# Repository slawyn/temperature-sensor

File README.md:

This project focuses on creating a simple usb-powered hardware that measures temperature.
*v1 - initial faulty design. CA CK have for 7-segment been switched
*v2 - improved doubled-sided design. Potentiometer replaced by an digital spi controller poti. Problem with the vias.
*v3 - wip

Use "Gerberlogix" to viewer gerber files.

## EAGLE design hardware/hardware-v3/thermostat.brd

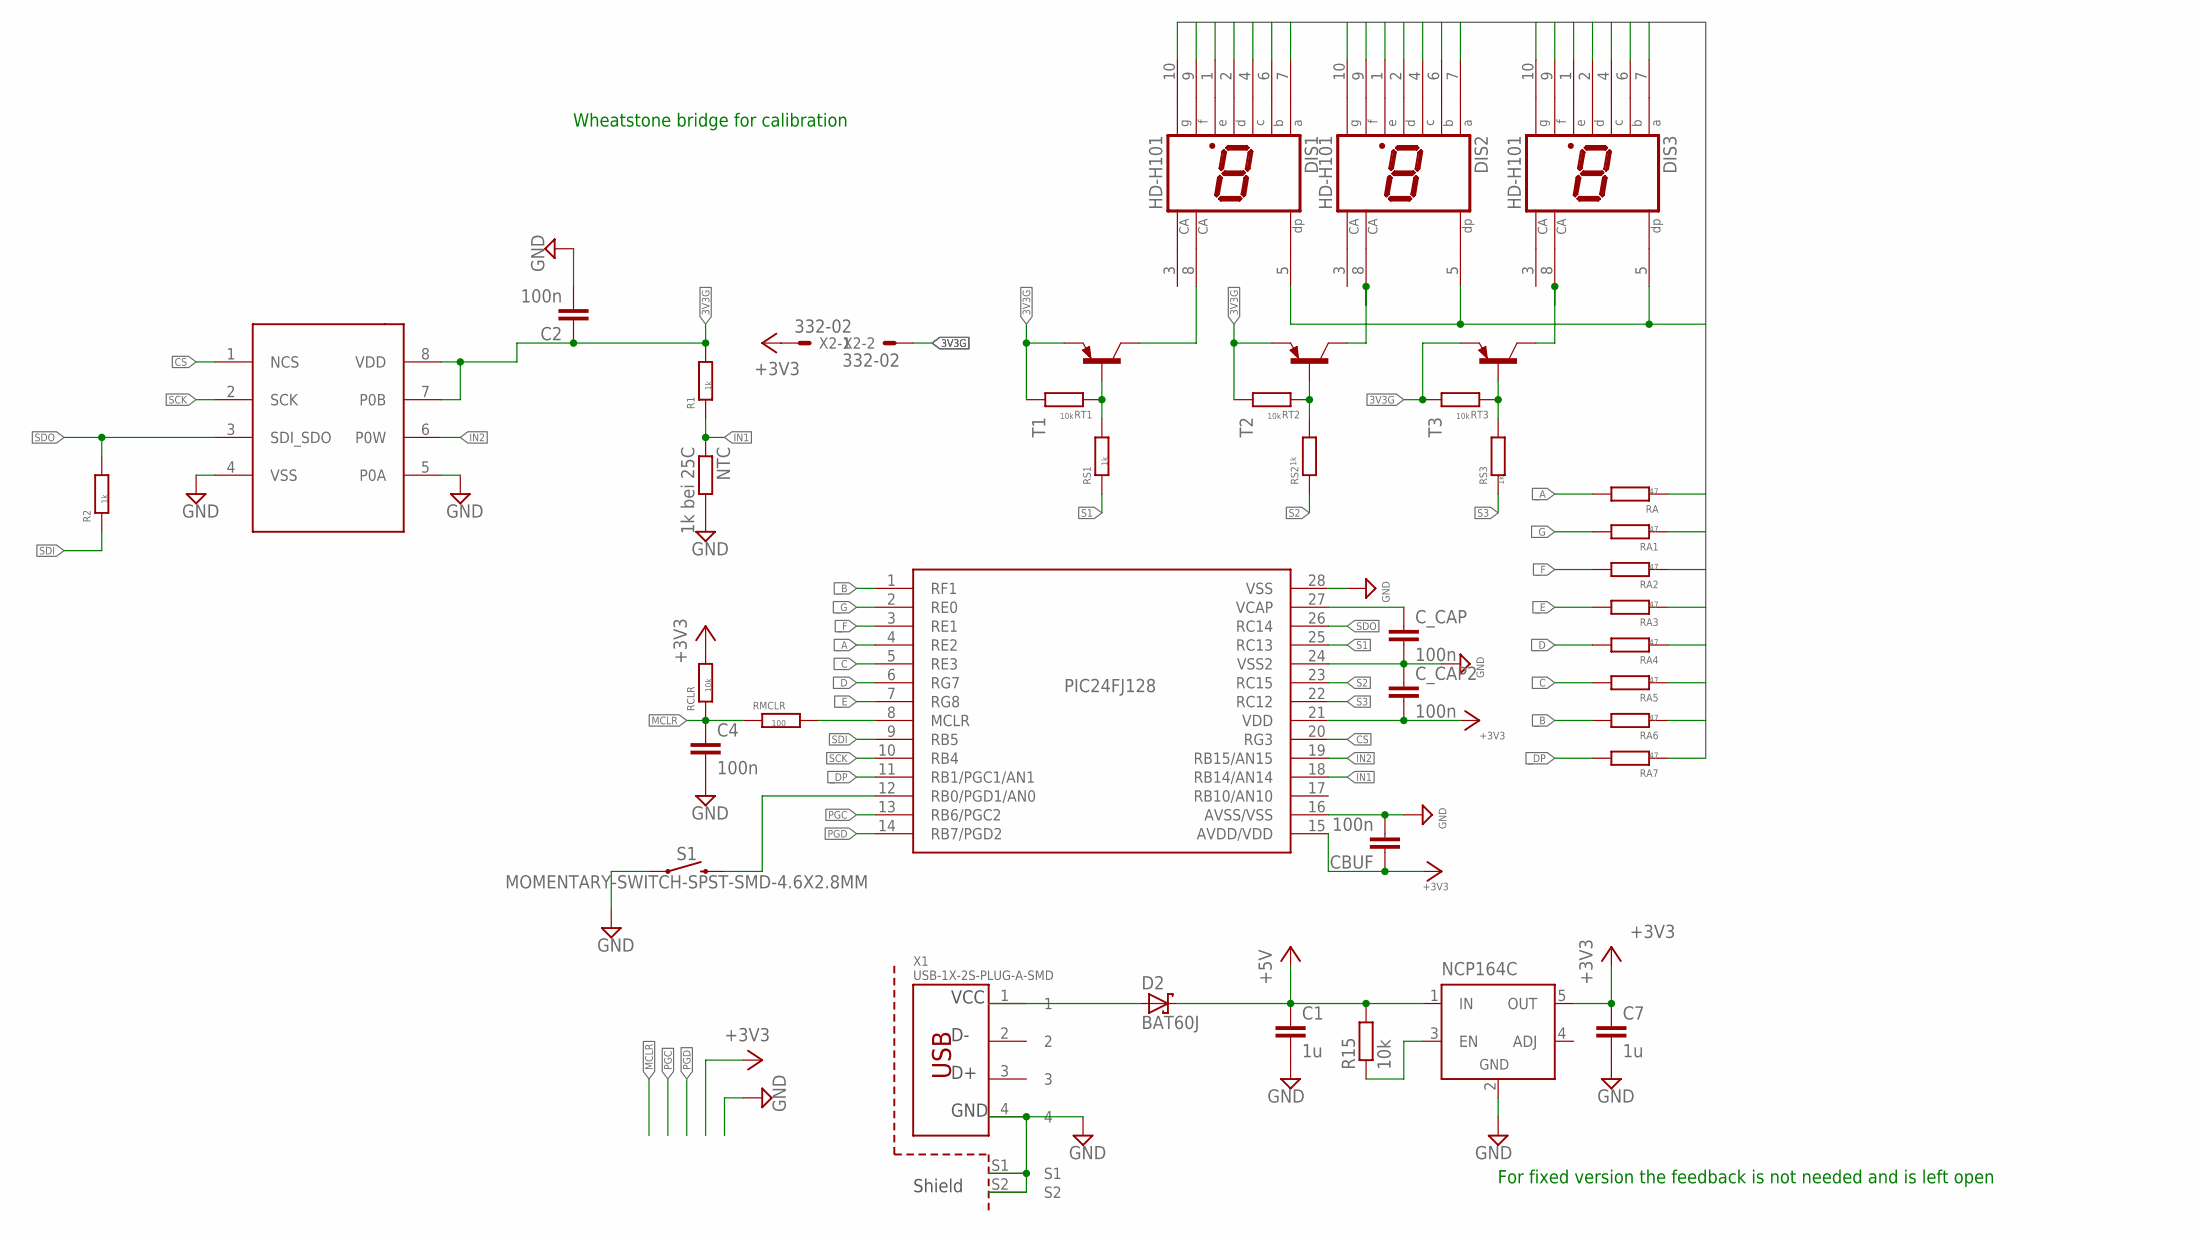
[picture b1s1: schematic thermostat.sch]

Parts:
C1, C7: 1u; C0603
C2, C4: 100n; C0603
CBUF: 100n; C0603
C_CAP, C_CAP2: 100n; C0603
D2: BAT60J; SOD323_ST
DIS1, DIS2, DIS3: HD-H101; HDSP-M
NCP164C: -; TSOP-5
NTC: 1k bei 25C; 0204V
R1, R2: 1k; R0603
R15: 10k; R0603
RA, RA1, RA2, RA3, RA4, RA5, RA6, RA7: 47; R0603
RCLR: 10k; R0603
RMCLR: 100; R0603
RS1, RS2, RS3: 1k; R0603
RT1, RT2, RT3: 10k; R0603
S1: MOMENTARY-SWITCH-SPST-SMD-4.6X2.8MM; TACTILE_SWITCH_SMD_4.6X2.8MM
T1, T2, T3: -PNP-SOT23-BCE; SOT23-BCE
U$1: MCP4151; SO-08
U$2: -; SSOP28
X1: USB-1X-2S-PLUG-A-SMD; USB-PLUG-A-SMD-2S
X2: 332-02

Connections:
3V3G: C2.1, R1.2, RT1.2, RT2.2, RT3.2, T1.E, T2.E, T3.E, U$1.7 (P0B), U$1.8 (VDD), X2.2
+3V3: C7.1, CBUF.1, C_CAP2.2, NCP164C.5 (OUT), RCLR.2, U$2.15 (AVDD/VDD), U$2.21 (VDD), X2.1
+5V: C1.1, D2.C, NCP164C.1 (IN), R15.2
A: DIS1.7 (A), DIS2.7 (A), DIS3.7 (A), RA.1
B: DIS1.6 (B), DIS2.6 (B), DIS3.6 (B), RA6.1
C: DIS1.4 (C), DIS2.4 (C), DIS3.4 (C), RA5.1
CS: U$1.1 (NCS), U$2.20 (RG3)
D: DIS1.2 (D), DIS2.2 (D), DIS3.2 (D), RA4.1
DP: DIS1.5 (DP), DIS2.5 (DP), DIS3.5 (DP), RA7.1
E: DIS1.1 (E), DIS2.1 (E), DIS3.1 (E), RA3.1
F: DIS1.9 (F), DIS2.9 (F), DIS3.9 (F), RA2.1
G: DIS1.10 (G), DIS2.10 (G), DIS3.10 (G), RA1.1
GND: C1.2, C2.2, C4.2, C7.2, CBUF.2, C_CAP.2, C_CAP2.1, NCP164C.2 (GND), NTC.2, S1.1, S1.2 (1), U$1.4 (VSS), U$1.5 (P0A), U$2.16 (AVSS/VSS), U$2.24 (VSS2), U$2.28 (VSS), X1.4, X1.S1, X1.S2
IN1: NTC.1, R1.1, U$2.18 (RB14/AN14)
IN2: U$1.6 (P0W), U$2.19 (RB15/AN15)
MCLR: C4.1, RCLR.1, RMCLR.1
unnamed: NCP164C.3 (EN), R15.1
unnamed: C_CAP.1, U$2.27 (VCAP)
unnamed: RS1.2, RT1.1, T1.B
unnamed: D2.A, X1.1
unnamed: RMCLR.2, U$2.8 (MCLR)
unnamed: RS3.2, RT3.1, T3.B
unnamed: RS2.2, RT2.1, T2.B
unnamed: DIS1.8 (CA), T1.C
unnamed: DIS2.8 (CA), T2.C
unnamed: DIS3.8 (CA), T3.C
unnamed: S1.3 (2), S1.4 (2), U$2.12 (RB0/PGD1/AN0)
PGC: U$2.13 (RB6/PGC2)
PGD: U$2.14 (RB7/PGD2)
S1: RS1.1, U$2.25 (RC13)
S2: RS2.1, U$2.23 (RC15)
S3: RS3.1, U$2.22 (RC12)
SCK: U$1.2 (SCK), U$2.10 (RB4)
SDI: R2.1, U$2.9 (RB5)
SDO: R2.2, U$1.3 (SDI_SDO), U$2.26 (RC14)
_A: RA.2, U$2.4 (RE2)
_B: RA6.2, U$2.1 (RF1)
_C: RA5.2, U$2.5 (RE3)
_D: RA4.2, U$2.6 (RG7)
_DP: RA7.2, U$2.11 (RB1/PGC1/AN1)
_E: RA3.2, U$2.7 (RG8)
_F: RA2.2, U$2.3 (RE1)
_G: RA1.2, U$2.2 (RE0)

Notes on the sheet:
For fixed version the feedback is not needed and is left open
Wheatstone bridge for calibration

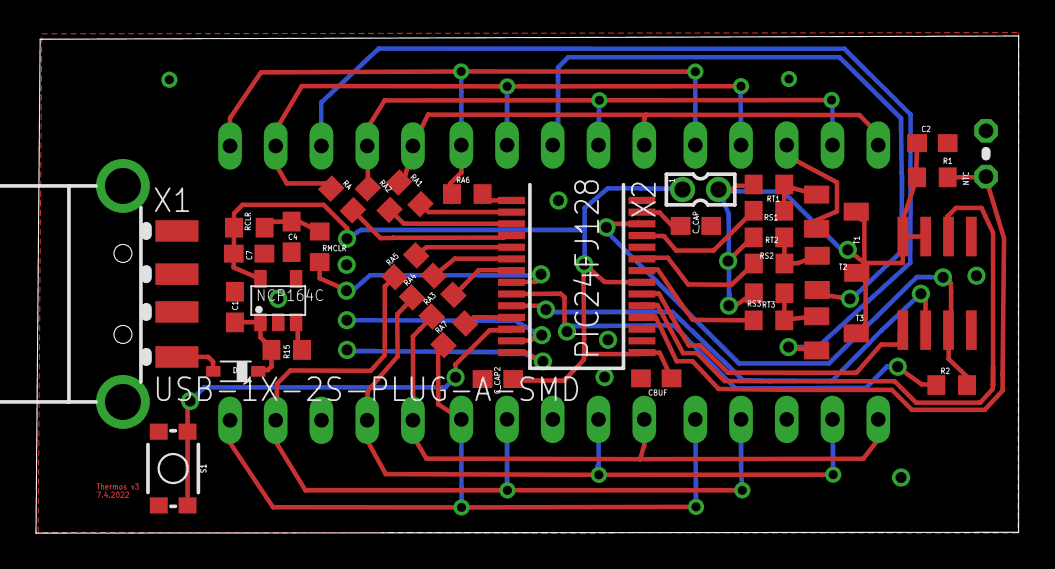
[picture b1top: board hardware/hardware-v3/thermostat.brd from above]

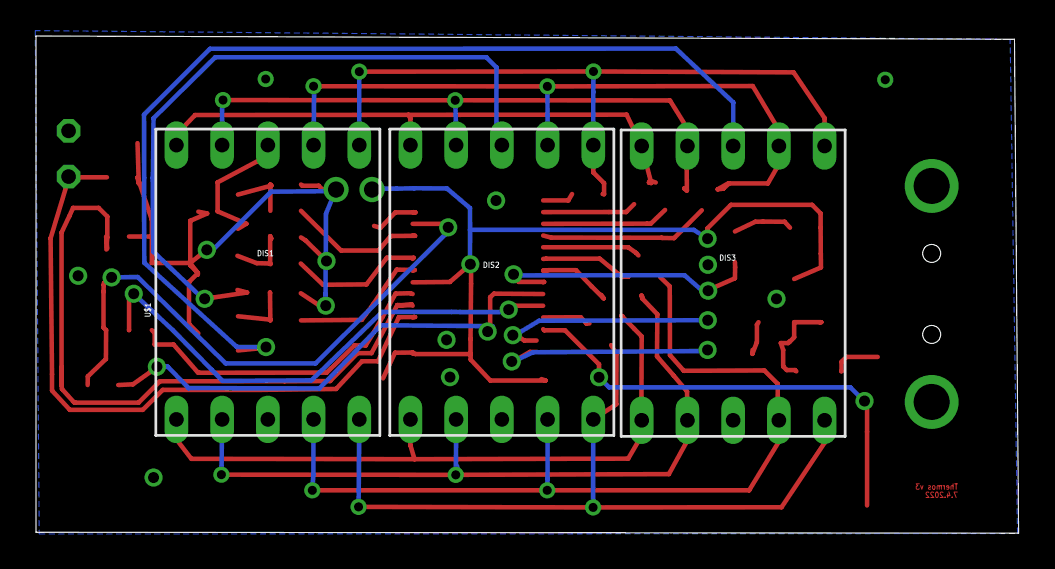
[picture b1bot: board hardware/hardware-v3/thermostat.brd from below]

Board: 2 copper layers, 54.6 x 27.6 mm, 40 parts (3 on the bottom side), 41 nets.

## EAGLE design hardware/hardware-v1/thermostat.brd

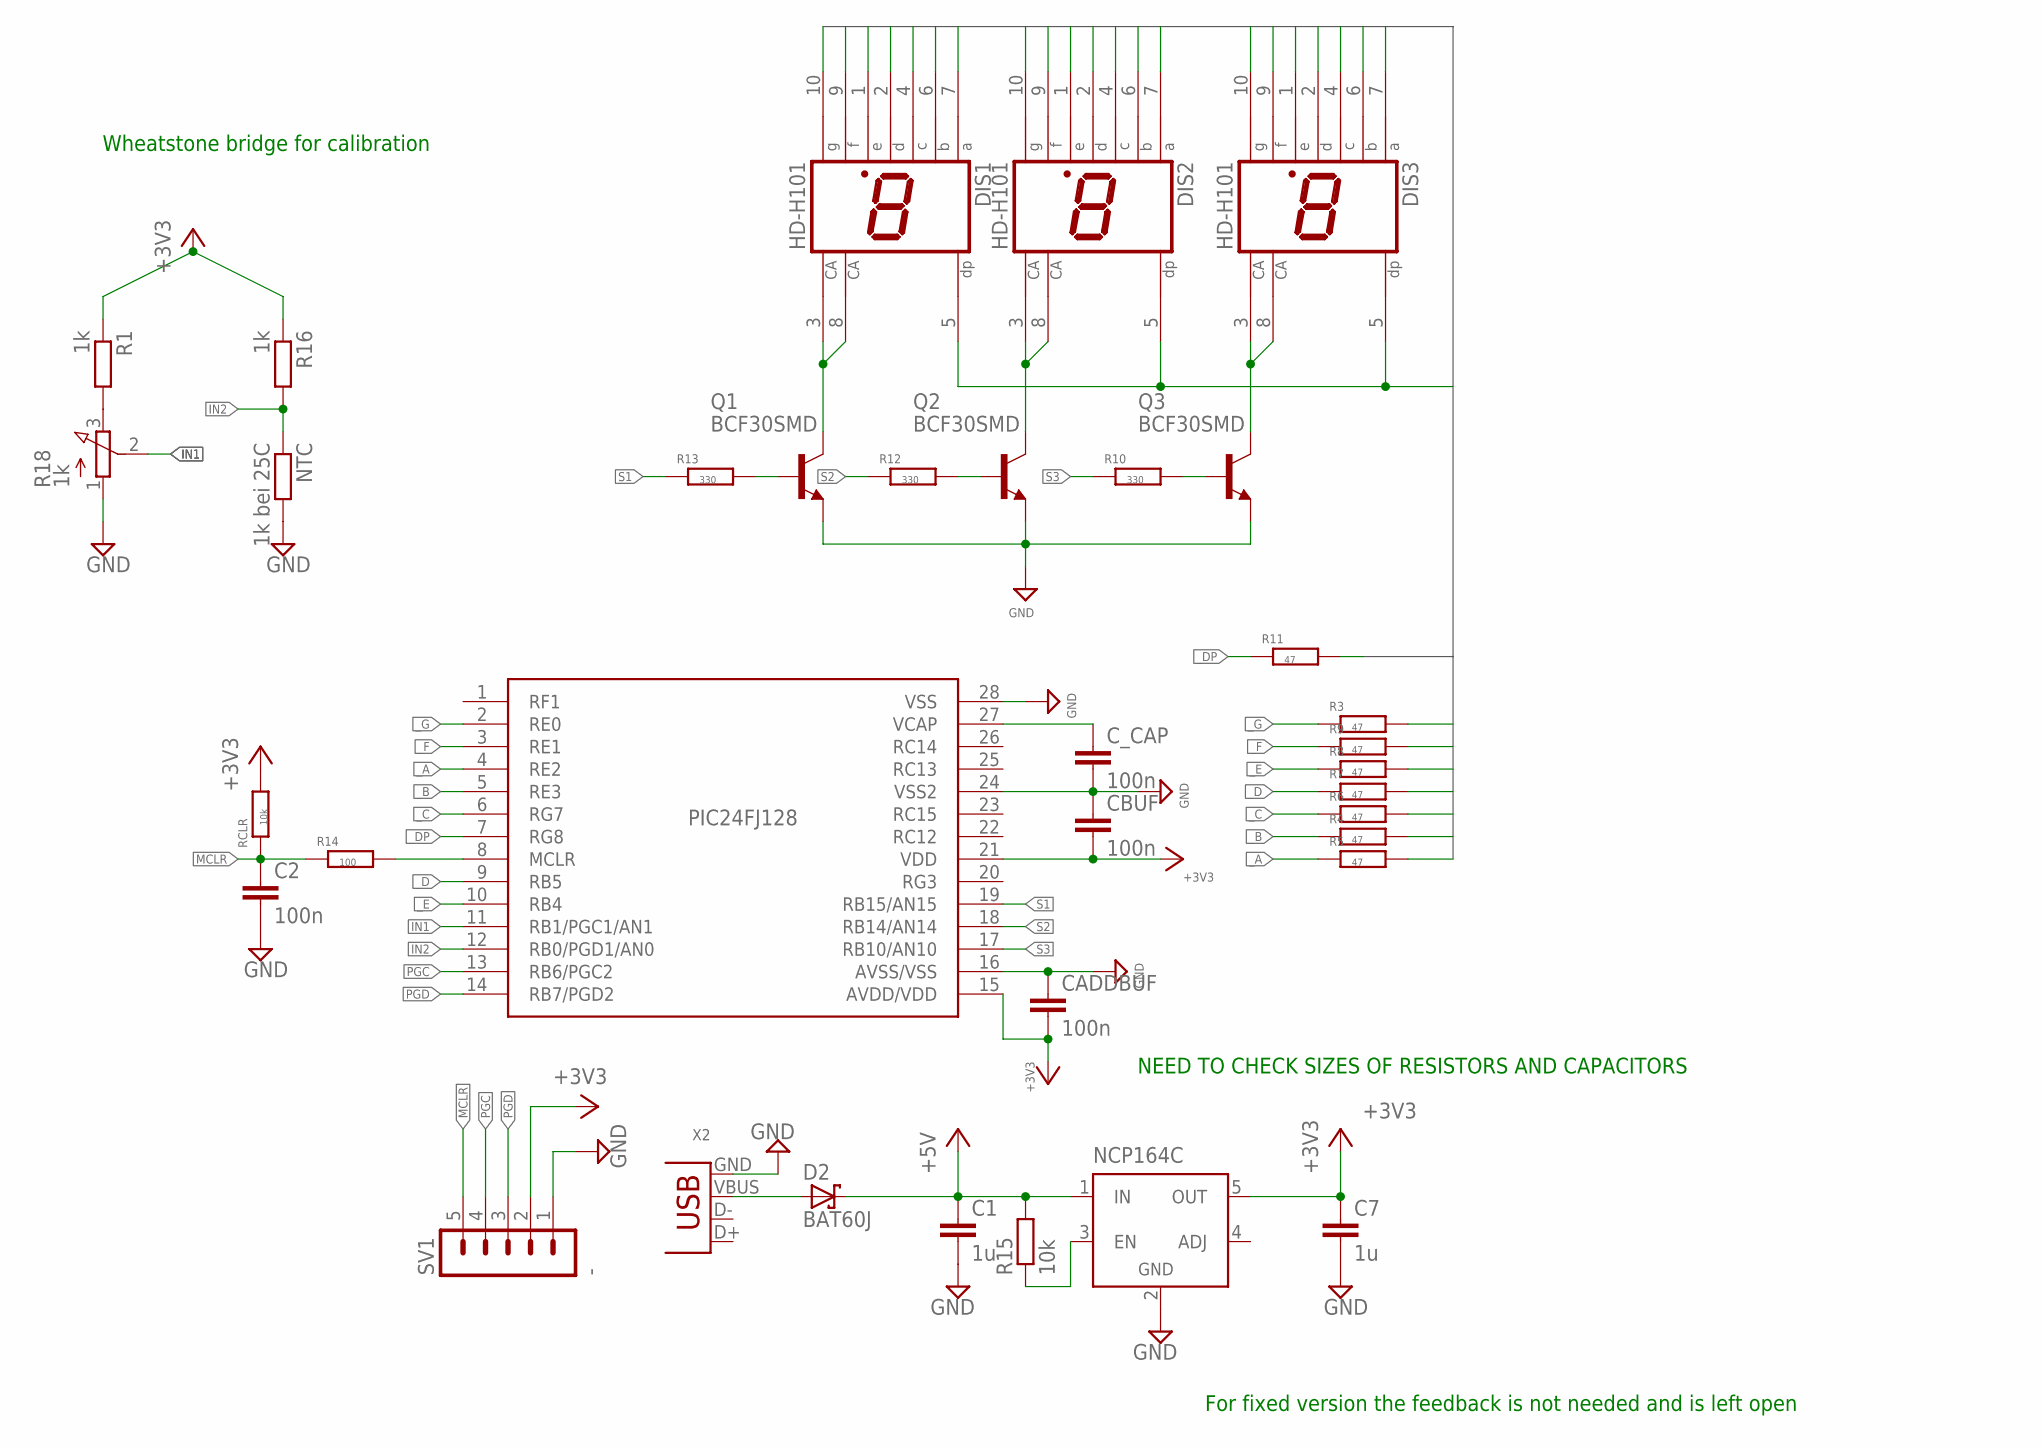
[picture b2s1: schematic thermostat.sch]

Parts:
C1, C7: 1u; C0603
C2: 100n; C0805
CADDBUF: 100n; C0603
CBUF: 100n; C0603
C_CAP: 100n; C0603
D2: BAT60J; SOD323_ST
DIS1, DIS2, DIS3: HD-H101; HDSP-M
NCP164C: -; TSOP-5
NTC: 1k bei 25C; 0204V
Q1, Q2, Q3: BCF30SMD; SOT23-BEC
R1, R16: 1k; R2010
R3, R4, R5, R6, R7, R8, R9, R11: 47; R0603
R10, R12, R13: 330; R0603
R14: 100; R0603
R15: 10k; R0603
R18: 1k; 3RP/1610N
RCLR: 10k; R0603
SV1: -; MA05-1
U$2: -; SSOP28
X2: -; USB-A-S

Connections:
+3V3: C7.1, CADDBUF.2, CBUF.2, NCP164C.5 (OUT), R1.1, R16.1, RCLR.2, SV1.2, U$2.15 (AVDD/VDD), U$2.21 (VDD)
+5V: C1.1, D2.C, NCP164C.1 (IN), R15.2
A: DIS1.7 (A), DIS2.7 (A), DIS3.7 (A), R5.2
B: DIS1.6 (B), DIS2.6 (B), DIS3.6 (B), R4.2
C: DIS1.4 (C), DIS2.4 (C), DIS3.4 (C), R6.2
D: DIS1.2 (D), DIS2.2 (D), DIS3.2 (D), R7.2
DP: DIS1.5 (DP), DIS2.5 (DP), DIS3.5 (DP), R11.2
E: DIS1.1 (E), DIS2.1 (E), DIS3.1 (E), R8.2
F: DIS1.9 (F), DIS2.9 (F), DIS3.9 (F), R9.2
G: DIS1.10 (G), DIS2.10 (G), DIS3.10 (G), R3.2
GND: C1.2, C2.2, C7.2, CADDBUF.1, CBUF.1, C_CAP.2, NCP164C.2 (GND), NTC.2, Q1.E, Q2.E, Q3.E, R18.1 (A), SV1.1, U$2.16 (AVSS/VSS), U$2.24 (VSS2), U$2.28 (VSS), X2.GND
IN1: R18.2 (S), U$2.11 (RB1/PGC1/AN1)
IN2: NTC.1, R16.2, U$2.12 (RB0/PGD1/AN0)
MCLR: C2.1, R14.1, RCLR.1, SV1.5
unnamed: NCP164C.3 (EN), R15.1
unnamed: R1.2, R18.3 (E)
unnamed: C_CAP.1, U$2.27 (VCAP)
unnamed: D2.A, X2.VBUS
unnamed: R14.2, U$2.8 (MCLR)
unnamed: DIS1.3 (CA), DIS1.8 (CA), Q1.C
unnamed: DIS2.3 (CA), DIS2.8 (CA), Q2.C
unnamed: DIS3.3 (CA), DIS3.8 (CA), Q3.C
unnamed: Q1.B, R13.2
unnamed: Q2.B, R12.2
unnamed: Q3.B, R10.2
PGC: SV1.4, U$2.13 (RB6/PGC2)
PGD: SV1.3, U$2.14 (RB7/PGD2)
S1: R13.1, U$2.19 (RB15/AN15)
S2: R12.1, U$2.18 (RB14/AN14)
S3: R10.1, U$2.17 (RB10/AN10)
_A: R5.1, U$2.4 (RE2)
_B: R4.1, U$2.5 (RE3)
_C: R6.1, U$2.6 (RG7)
_D: R7.1, U$2.9 (RB5)
_DP: R11.1, U$2.7 (RG8)
_E: R8.1, U$2.10 (RB4)
_F: R9.1, U$2.3 (RE1)
_G: R3.1, U$2.2 (RE0)

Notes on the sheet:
NEED TO CHECK SIZES OF RESISTORS AND CAPACITORS
For fixed version the feedback is not needed and is left open
Wheatstone bridge for calibration

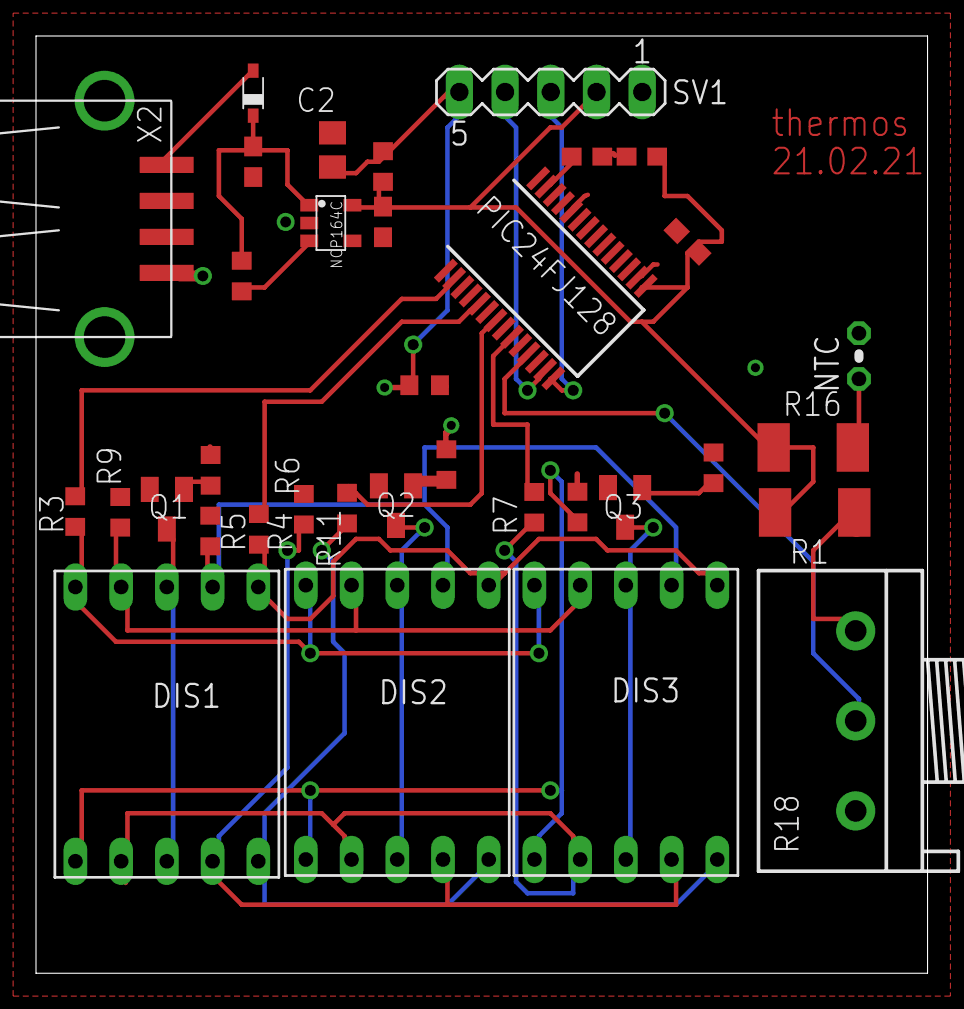
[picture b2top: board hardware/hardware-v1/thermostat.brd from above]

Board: 2 copper layers, 49.5 x 52.1 mm, 35 parts (0 on the bottom side), 38 nets.

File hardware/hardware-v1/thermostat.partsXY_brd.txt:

Parts List with XY on brd
i	Name	Package	Value	(X Y) [mil]	Angle	Layer	Height
[00]	C1	C0603	1u	( 461.024 1617.717)	  270.00	 1	*
[01]	C2	C0805	100n	( 598.425 1700.787)	   90.00	 1	*
[02]	C7	C0603	1u	( 709.055 1543.307)	  270.00	 1	*
[03]	CADDBUF	C0603	100n	(1401.181 1501.181)	    0.00	 1	*
[04]	CBUF	C0603	100n	(1275.197 1686.220)	    0.00	 1	*
[05]	C_CAP	C0603	100n	(1155.118 1686.220)	    0.00	 1	*
[06]	D2	SOD323_ST	BAT60J	( 354.331 1661.417)	  180.00	 1	*
[07]	DIS1	HDSP-M	HD-H101	( 236.220  444.882)	    0.00	 1	*
[08]	DIS2	HDSP-M	HD-H101	( 740.157  448.819)	    0.00	 1	*
[09]	DIS3	HDSP-M	HD-H101	(1240.157  448.819)	    0.00	 1	*
[10]	NCP164C	TSOP-5	-	( 594.882 1540.945)	  270.00	 1	*
[11]	NTC	0204V	1k bei 25C	(1740.945 1307.480)	   90.00	 1	*
[12]	Q1	SOT23-BEC	BCF30SMD	( 236.220  914.961)	  180.00	 1	*
[13]	Q2	SOT23-BEC	BCF30SMD	( 737.402  922.835)	  180.00	 1	*
[14]	Q3	SOT23-BEC	BCF30SMD	(1238.583  918.898)	  180.00	 1	*
[15]	R1	R2010	1k	(1653.150  907.874)	    0.00	 1	*
[16]	R3	R0603	47	(  35.827  909.843)	  270.00	 1	*
[17]	R4	R0603	47	( 437.402  870.866)	  270.00	 1	*
[18]	R5	R0603	47	( 331.102  867.323)	  270.00	 1	*
[19]	R6	R0603	47	( 535.827  914.961)	  270.00	 1	*
[20]	R7	R0603	47	(1039.764  919.291)	  270.00	 1	*
[21]	R8	R0603	47	(1134.252  919.685)	  270.00	 1	*
[22]	R9	R0603	47	( 134.252  908.268)	  270.00	 1	*
[23]	R10	R0603	330	(1331.890 1005.512)	  270.00	 1	*
[24]	R11	R0603	47	( 630.315  917.323)	  270.00	 1	*
[25]	R12	R0603	330	( 847.638 1012.598)	  270.00	 1	*
[26]	R13	R0603	330	( 331.890 1000.000)	  270.00	 1	*
[27]	R14	R0603	100	( 800.000 1186.220)	    0.00	 1	*
[28]	R15	R0603	10k	( 421.654 1473.228)	  270.00	 1	*
[29]	R16	R2010	1k	(1652.362 1053.543)	    0.00	 1	*
[30]	R18	3RP/1610N	1k	(1742.913  451.969)	   90.00	 1	*
[31]	RCLR	R0603	10k	( 709.055 1664.567)	  270.00	 1	*
[32]	SV1	MA05-1	-	(1075.984 1827.559)	  180.00	 1	*
[33]	U$2	SSOP28	-	(1064.961 1420.079)	  315.00	 1	*
[34]	X2	USB-A-S	-	(  86.614 1543.307)	    0.00	 1	*

Number of parts:35

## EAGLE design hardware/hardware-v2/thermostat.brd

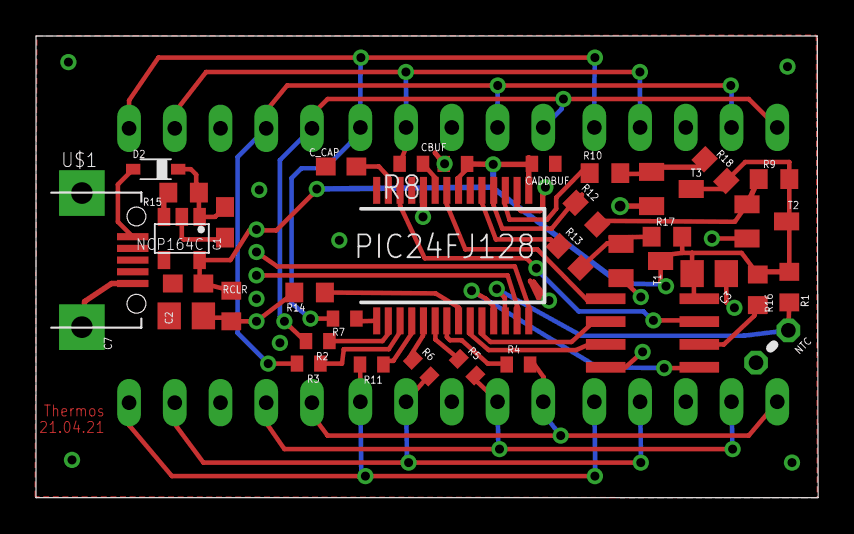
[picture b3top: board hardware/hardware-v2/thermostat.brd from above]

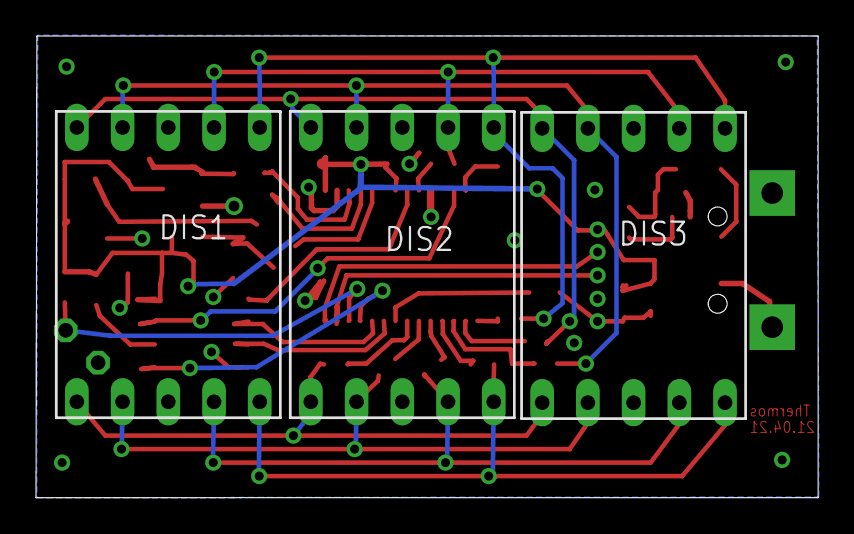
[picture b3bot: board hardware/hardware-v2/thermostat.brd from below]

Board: 4 copper layers, 43.5 x 25.6 mm, 38 parts (3 on the bottom side), 40 nets.

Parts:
C1, C7: 1u; C0603
C2, C3: 100n; C0805
CADDBUF: 100n; C0402
CBUF: 100n; C0402
C_CAP: 100n; C0603
D2: BAT60J; SOD323_ST
DIS1, DIS2, DIS3: HD-H101; HDSP-M
NCP164C: -; TSOP-5
NTC: 1k bei 25C; 0204V
R1, R10, R12, R13, R16: 1k; R0603
R2, R3, R4, R5, R6, R7, R8, R11: 47; R0402
R9, R15, R17, R18: 10k; R0603
R14: 100; R0603
RCLR: 10k; R0603
T1, T2, T3: SOT23-BCE
U$1: MICRO-USB
U$2: -; SSOP28
U$3: MCP4141-103; SO-08

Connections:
+3V3: C3.2, C7.1, CADDBUF.2, CBUF.2, NCP164C.5, R1.2, R9.2, R16.2, R17.2, R18.2, RCLR.2, T1.E, T2.E, T3.E, U$2.15, U$2.21, U$3.8
+5V: C1.1, D2.C, NCP164C.1, R15.2
A: DIS1.7, DIS2.7, DIS3.7, R8.2
B: DIS1.6, DIS2.6, DIS3.6, R7.2
C: DIS1.4, DIS2.4, DIS3.4, R6.2
CS: U$2.22, U$3.1
D: DIS1.2, DIS2.2, DIS3.2, R5.2
DP: DIS1.5, DIS2.5, DIS3.5, R11.2
E: DIS1.1, DIS2.1, DIS3.1, R4.2
F: DIS1.9, DIS2.9, DIS3.9, R3.2
G: DIS1.10, DIS2.10, DIS3.10, R2.2
GND: C1.2, C2.2, C3.1, C7.2, CADDBUF.1, CBUF.1, C_CAP.2, NCP164C.2, NTC.2, U$1.5, U$1.GND1, U$1.GND2, U$2.16, U$2.24, U$2.28, U$3.4
IN1: U$2.11, U$3.5
IN2: NTC.1, R1.1, U$2.12
MCLR: C2.1, R14.1, RCLR.1
unnamed: NCP164C.3, R15.1
unnamed: R16.1, U$3.6
unnamed: C_CAP.1, U$2.27
unnamed: R13.2, R17.1, T1.B
unnamed: D2.A, U$1.1
unnamed: R14.2, U$2.8
unnamed: R10.2, R18.1, T3.B
unnamed: R9.1, R12.2, T2.B
unnamed: DIS1.3, DIS1.8, T1.C
unnamed: DIS2.3, DIS2.8, T2.C
unnamed: DIS3.3, DIS3.8, T3.C
S1: R13.1, U$2.19
S2: R12.1, U$2.18
S3: R10.1, U$2.17
SCK: U$2.10, U$3.2
SDI: U$2.9, U$3.3
SDO: U$2.26, U$3.7
_A: R8.1, U$2.23
_B: R7.1, U$2.1
_C: R6.1, U$2.5
_D: R5.1, U$2.6
_DP: R11.1, U$2.4
_E: R4.1, U$2.7
_F: R3.1, U$2.3
_G: R2.1, U$2.2

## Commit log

2022-04-07 New Layout
2022-05-27 +Added .pdf

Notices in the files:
parts and their libraries:
SparkFun-Switches: Licensing: Creative Commons ShareAlike 4.0 International - https://creativecommons.org/licenses/by-sa/4.0
